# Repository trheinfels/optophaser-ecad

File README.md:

# Optophaser Guitar Pedal - ECAD

This repository contains the ECAD files for an eight stage optophaser guitar effect pedal designed in KiCad.

# Features

The phaser is based around well-known analog circuitry. What sets it apart from commercially available units is the large number of controls, the configurability (there are multiple combinations of voices), and the digital synthesis of the LFO signal. Both are detailed in the following sections.

## Controls

Beside a switch which allows for selecting the number of phaser stages and a tap tempo button, the controls comprise five potentiometers:

- Waveform: Blends between different LFO wave forms
- Frequency: LFO frequency
- Range: LFO amplitude (i.e., the frequency range the phaser spans)
- Depth: Gain for the mix (i.e., the amount of phasing effect)
- Resonance: Feedback gain (makes the phaser sound more *nasty*)

## Configurability

While not intended to be exposed to the case, there are multiple configuration options which can be selected via jumpers:

- Dir: Direction in which the LFO modulates the comb filter frequencies
- Out1: First tap of the phaser stage switch. Uses either the signal after the second or the sixth phasing stage
- Out2: Second tap of the phaser stage switch. Uses either the signal after the fourth or the eigth phasing stage
- ResO: Selects the origin of the resonance feedback signal. Either after the fourth, sixth, or eigth stage
- ResI: Selects the destination of the resonance feedback signal. Insert it either into the first or second phasing stage

## MCU-based LFO

Instead of an analog circuitry, this phaser unit uses an STM32 microcontroller for generating low-frequency oscillator signal which modulates the comb filter frequencies. This allows for implementing unusual features such as

- Generating arbitrary waveforms and blending them on the fly
- Tap tempo
- Expression pedal input (either resistive or via control voltage)

For the sake of usability, the MCU can be connected via USB. This allows for firmware updates and can potentially be used to upload arbitrary waveforms to the phaser.

## License

The ECAD files are licensed under CC-BY-SA, see [COPYING](COPYING).

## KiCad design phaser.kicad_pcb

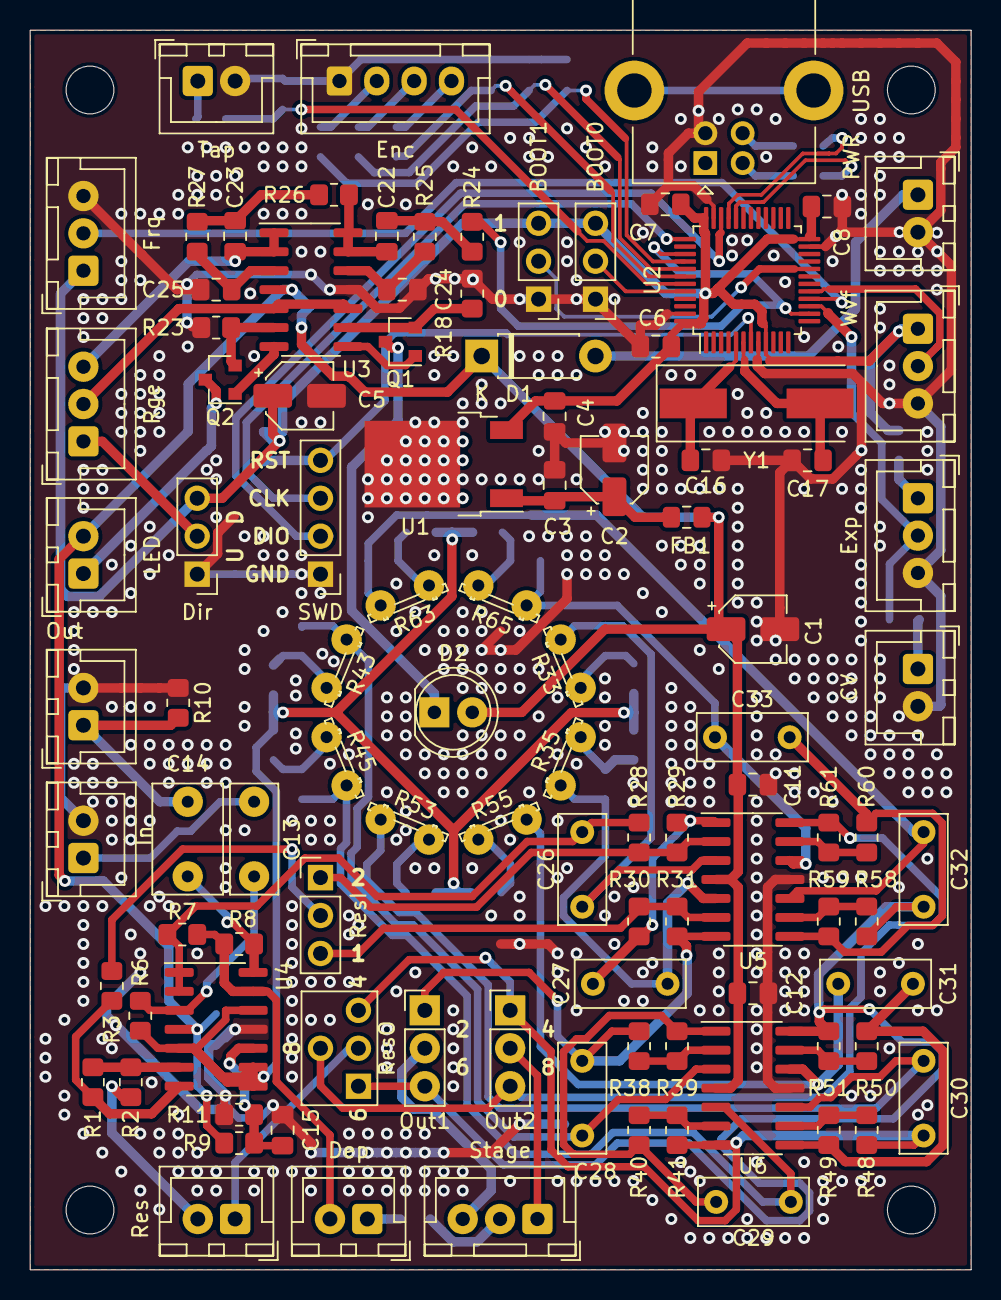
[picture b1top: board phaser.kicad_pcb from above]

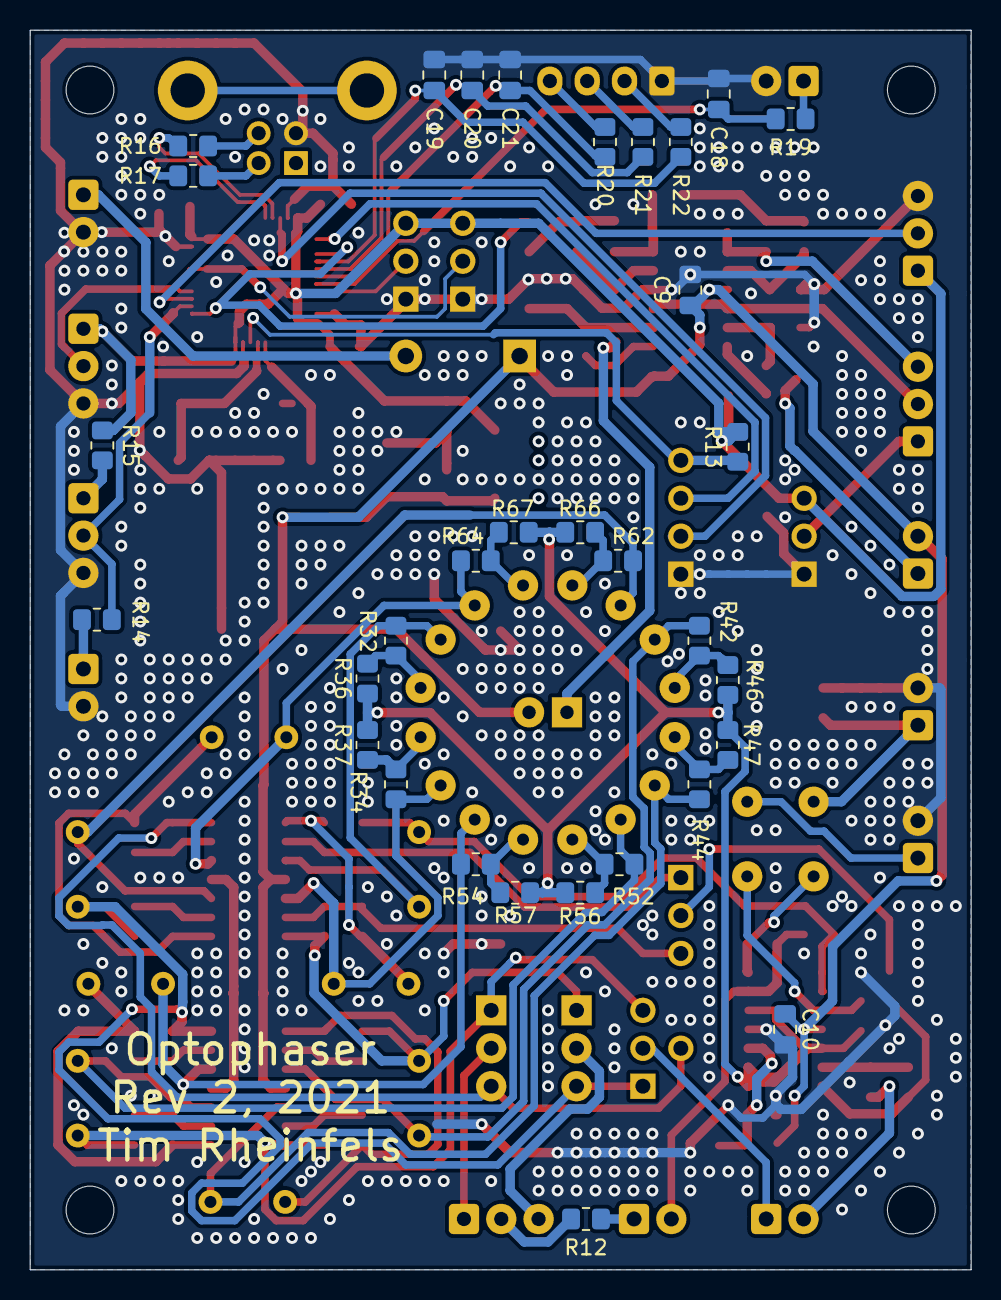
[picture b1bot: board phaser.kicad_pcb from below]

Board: 2 copper layers, 63.0 x 83.0 mm, 137 parts (32 on the bottom side), 93 nets.

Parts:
C1, C2, C5: 10u; CP_Elec_4x5.4
C3, C4, C6, C7, C8, C9, C10, C11, C12, C18, C19, C20, C21: 100n; C_0805_2012Metric_Pad1.18x1.45mm_HandSolder
C13, C26, C27, C28, C29, C30, C31, C32, C33: 22n; C_Rect_L7.2mm_W3.0mm_P5.00mm_FKS2_FKP2_MKS2_MKP2
C14: 68n; C_Rect_L7.2mm_W4.5mm_P5.00mm_FKS2_FKP2_MKS2_MKP2
C15: 22n; C_0805_2012Metric_Pad1.18x1.45mm_HandSolder
C16, C17: 15p; C_0805_2012Metric_Pad1.18x1.45mm_HandSolder
C22, C23, C24, C25: 15n; C_0805_2012Metric_Pad1.18x1.45mm_HandSolder
D1: SB120; D_DO-41_SOD81_P7.62mm_Horizontal
D2: LED; LED_D5.0mm_Clear
FB1: Ferrite_Bead; L_0805_2012Metric_Pad1.15x1.40mm_HandSolder
H1, H2, H3, H4: MountingHole_3.2mm_M3
J1: Res; JST_XH_B2B-XH-A_1x02_P2.50mm_Vertical
J2: PWR; JST_XH_B2B-XH-A_1x02_P2.50mm_Vertical
J3: In; JST_XH_B2B-XH-A_1x02_P2.50mm_Vertical
J4: Out; JST_XH_B2B-XH-A_1x02_P2.50mm_Vertical
J5: Out1; PinHeader_1x03_P2.54mm_Vertical
J6: Out2; PinHeader_1x03_P2.54mm_Vertical
J7: Stage; JST_XH_B3B-XH-A_1x03_P2.50mm_Vertical
J8: Dep; JST_XH_B2B-XH-A_1x02_P2.50mm_Vertical
J9: CV; JST_XH_B2B-XH-A_1x02_P2.50mm_Vertical
J10: SWD; PinHeader_1x04_P2.54mm_Vertical
J11: Dir; PinHeader_1x03_P2.54mm_Vertical
J12: Exp; JST_XH_B3B-XH-A_1x03_P2.50mm_Vertical
J13: Rge; JST_XH_B3B-XH-A_1x03_P2.50mm_Vertical
J14: USB; USB_B_Lumberg_2411_02_Horizontal
J15: Frq; JST_XH_B3B-XH-A_1x03_P2.50mm_Vertical
J16: Wvf; JST_XH_B3B-XH-A_1x03_P2.50mm_Vertical
J17: Tap; JST_XH_B2B-XH-A_1x02_P2.50mm_Vertical
J18: BOOT0; PinHeader_1x03_P2.54mm_Vertical
J19: LED; JST_XH_B2B-XH-A_1x02_P2.50mm_Vertical
J20: BOOT1; PinHeader_1x03_P2.54mm_Vertical
J21: Enc; JST_XH_B4B-XH-A_1x04_P2.50mm_Vertical
J22: ResI; PinHeader_1x03_P2.54mm_Vertical
JP1: ResO; Sel3
Q1, Q2: BC846; SOT-23
R1: 1k; R_0805_2012Metric_Pad1.20x1.40mm_HandSolder
R2: 2k; R_0805_2012Metric_Pad1.20x1.40mm_HandSolder
R3, R7, R8, R9, R11, R12, R13, R19, R20, R21, R22, R28, R29, R30, R31, R36, R37, R38, R39, R40, R41, R46, R47, R48, R49, R50, R51, R56, R57, R58, R59, R60, R61, R66, R67: 10k; R_0805_2012Metric_Pad1.20x1.40mm_HandSolder
R6: 470k; R_0805_2012Metric_Pad1.20x1.40mm_HandSolder
R10: 150k; R_0805_2012Metric_Pad1.20x1.40mm_HandSolder
R14, R15: 100; R_0805_2012Metric_Pad1.20x1.40mm_HandSolder
R16, R17: 22; R_0805_2012Metric_Pad1.20x1.40mm_HandSolder
R18, R23: 165; R_0805_2012Metric_Pad1.20x1.40mm_HandSolder
R24, R25, R26, R27, R32, R34, R42, R44, R52, R54, R62, R64: 100k; R_0805_2012Metric_Pad1.20x1.40mm_HandSolder
R33, R35, R43, R45, R53, R55, R63, R65: 2k-230k; R_LDR_5.2x5.2mm_P3.5mm_Horizontal
U1: LF33; TO-252-2
U2: STM32L151CBTxA; LQFP-48_7x7mm_P0.5mm
U3: LM324; SOIC-14_3.9x8.7mm_P1.27mm
U4, U5, U6: TL074; SOIC-14_3.9x8.7mm_P1.27mm
Y1: 16 MHz; Crystal_SMD_HC49-SD

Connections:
+3V3: C4.1, C5.1, C6.2, C7.2, C8.2, J11.3, J15.1, J16.1, J18.3, J20.3, R13.2, R15.1, U1.3, U2.9, U2.24, U2.36, U2.48
+9V: C1.1, C9.1, C10.1, C11.1, C12.1, D1.1, D2.2, FB1.2, J19.2, R9.1, U3.4, U4.4, U5.4, U6.4
/low_pass/y: C23.1, J13.3, U3.1, U3.2
/stage_12/res1: J22.1, R28.1, R29.2, U5.2
/stage_12/res2: J22.3, R30.1, R31.2, U5.6
/stage_12/u: C26.2, R7.2, R28.2, U4.1, U4.2
/stage_34/u: C28.2, J5.1, R31.1, R38.2, U5.7
/stage_56/u: C30.2, J6.1, JP1.3, R41.1, R48.2, U6.7
/stage_78/u: C32.2, J5.3, JP1.1, R51.1, R58.2, U6.14
/stage_78/y: J6.3, JP1.2, R61.1, U5.14
BOOT0: J18.2, U2.44
BOOT1: J20.2, U2.20
CV: J12.2, R14.2, U2.15
D+: R16.2, U2.33
D-: R17.2, U2.32
DAC: R24.2, U2.14, U2.39
ENC_A: C19.1, R22.1, U2.40
ENC_B: C20.1, R21.1, U2.41
ENC_S: C21.1, R20.1, U2.42
Frq: J15.2, U2.16
GND: C1.2, C2.2, C3.2, C4.2, C5.2, C6.1, C7.1, C8.1, C9.2, C10.2, C11.2, C12.2, C15.2, C16.1, C17.1, C18.2, C19.2, C20.2, C21.2, C24.1, C25.1, J2.2, J3.2, J4.2, J9.2, J10.1, J11.1, J12.3, J14.4, J15.3, J16.3, J17.2, J18.1, J20.1, J21.1, R10.1, R11.2, R18.1, R23.1, U1.2, U2.8, U2.23, U2.35, U2.47, U3.11, U4.11, U5.11, U6.11
GNDA: R6.1, R36.2, R37.2, R46.2, R47.2, R56.2, R57.2, R66.2, R67.2, U4.5, U4.8, U4.9, U4.12
NRST: J10.4, R13.1, U2.7
unnamed: C2.1, C3.1, FB1.1, U1.1
unnamed: C13.1, R6.2, U4.3
unnamed: C13.2, J3.1
unnamed: C14.1, J4.1, R10.2
unnamed: C14.2, R8.1, U4.14
unnamed: C15.1, R9.2, R11.1, U4.10
unnamed: C16.2, U2.5, Y1.1
unnamed: C17.2, U2.6, Y1.2
unnamed: C22.1, R26.2, U3.13, U3.14
unnamed: C22.2, R24.1, R25.2
unnamed: C23.2, R26.1, R27.2
unnamed: C24.2, R25.1, U3.12
unnamed: C25.2, R27.1, U3.3
unnamed: C26.1, R32.1, R33.2, U5.3
unnamed: C27.1, R34.1, R35.1, U5.5
unnamed: C27.2, R29.1, R30.2, U5.1
unnamed: C28.1, R42.1, R43.1, U6.3
unnamed: C29.1, R44.1, R45.2, U6.5
unnamed: C29.2, R39.1, R40.2, U6.1
unnamed: C30.1, R52.1, R53.1, U6.10
unnamed: C31.1, R54.1, R55.2, U6.12
unnamed: C31.2, R49.1, R50.2, U6.8
unnamed: C32.1, R62.1, R63.2, U5.10
unnamed: C33.1, R64.1, R65.1, U5.12
unnamed: C33.2, R59.1, R60.2, U5.8
unnamed: D1.2, J2.1
unnamed: D2.1, Q1.3
unnamed: J1.1, JP1.4
unnamed: J1.2, R2.1
unnamed: J5.2, J7.3
unnamed: J6.2, J7.1
unnamed: J7.2, R12.2
unnamed: J8.1, R12.1
unnamed: J8.2, R7.1, R8.2, U4.13
unnamed: J9.1, R14.1
unnamed: J11.2, J13.1
unnamed: J12.1, R15.2
unnamed: J13.2, U3.5, U3.10
unnamed: J14.2, R17.1
unnamed: J14.3, R16.1
unnamed: J17.1, R19.2
unnamed: J19.1, Q2.3
unnamed: J21.2, R22.2
unnamed: J21.3, R21.2
unnamed: J21.4, R20.2
unnamed: J22.2, R3.2
unnamed: Q1.1, U3.8
unnamed: Q1.2, R18.2, U3.9
unnamed: Q2.1, U3.7
unnamed: Q2.2, R23.2, U3.6
unnamed: R1.1, R2.2, U4.6
unnamed: R1.2, R3.1, U4.7
unnamed: R32.2, R33.1, R36.1
unnamed: R34.2, R35.2, R37.1
unnamed: R38.1, R39.2, U6.2
unnamed: R40.1, R41.2, U6.6
unnamed: R42.2, R43.2, R46.1
unnamed: R44.2, R45.1, R47.1
unnamed: R48.1, R49.2, U6.9
unnamed: R50.1, R51.2, U6.13
unnamed: R52.2, R53.2, R56.1
unnamed: R54.2, R55.1, R57.1
unnamed: R58.1, R59.2, U5.9
unnamed: R60.1, R61.2, U5.13
unnamed: R62.2, R63.1, R66.1
unnamed: R64.2, R65.2, R67.1
SWCLK: J10.3, U2.37
SWDIO: J10.2, U2.34
Tap: C18.1, R19.1, U2.43
Wvf: J16.2, U2.17

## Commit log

2023-06-05 Revision 2
    See changelog.txt
2023-06-05 Revision 1
2023-06-05 COPYING: add CC-BY-SA license text
2023-06-05 README.md: add a little description
2023-06-06 README.md: some minor improvements
